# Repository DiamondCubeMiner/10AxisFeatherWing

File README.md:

# 10AxisFeatherWing #
A 10-DOF Featherwing, powered by BNO055 and BME280.

## Description ##
This featherwing uses I2C to connect both the IMU (BNO055) and the altimeter (BME280) to the Feather.
I made this to design projects that require a 10-DOF IMU in a tiny package where breakouts can affect the weight a lot and may not be a good option, such as a quadcopter, a model plane, or a model rocket.

## Drivers ##
This project is designed to use [Adafruit Unified Sensor Drivers](https://github.com/adafruit/Adafruit_Sensor).
  - [Adafruit_BNO055](https://github.com/adafruit/Adafruit_BNO055)
  - [Adafruit_BME280_Library](https://github.com/adafruit/Adafruit_BME280_Library/)

If you are experiencing problems with the Adafruit_BME280_Library, you may use Seeed Studio's [Grove_BME280](https://github.com/Seeed-Studio/Grove_BME280) drivers. It has been tested to work with the 10AxisFeatherWing.

## Thanks ##
This project is derived from the following projects:
  - [Adafruit-ADXL343-ADT7410-Featherwing-PCB](https://github.com/adafruit/Adafruit-ADXL343-ADT7410-Featherwing-PCB)
  - [Adafruit-BNO055-Breakout-PCB](https://github.com/adafruit/Adafruit-BNO055-Breakout-PCB)
  - [Adafruit-BME280-Breakout-PCB](https://github.com/adafruit/Adafruit-BME280-Breakout-PCB)

Thanks to Adafruit for their open-source schematics!

Thanks to ppelleti for the awesome FeatherWing Template!

[FeatherWing-template-KiCad](https://github.com/ppelleti/FeatherWing-template-KiCad)

## License ##
This work is licensed under the Creative Commons Attribution-ShareAlike 3.0 Unported License. To view a copy of this license, visit http://creativecommons.org/licenses/by-sa/3.0/ or by opening license.txt included in this project.

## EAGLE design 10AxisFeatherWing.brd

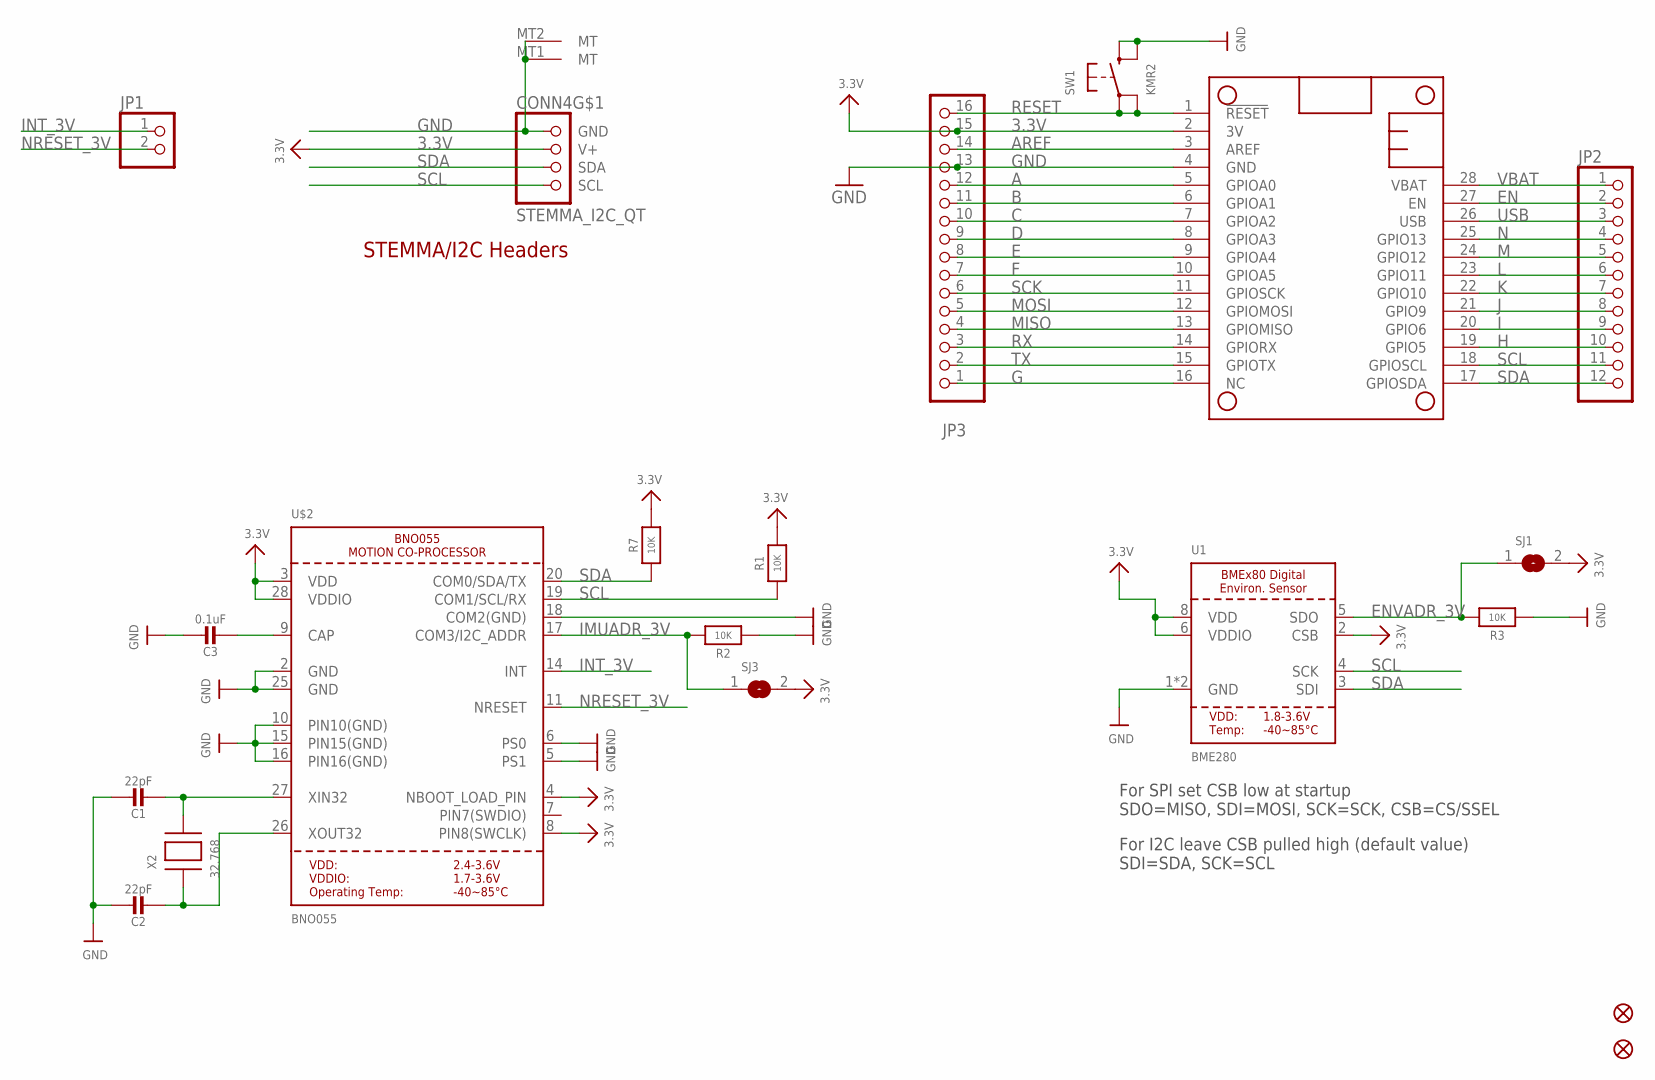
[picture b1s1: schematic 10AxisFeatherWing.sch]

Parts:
C1, C2: 22pF; 0603-NO
C3: 0.1uF; 0603-NO
CONN4: STEMMA_I2C_QT; JST_SH4
FID1, FID2: FIDUCIAL_1MM
JP1: HEADER-1X2ROUND; 1X02_ROUND
JP2: HEADER-1X12; 1X12_ROUND
JP3: HEADER-1X16ROUND; 1X16_ROUND
MS1: FEATHERWING
R1, R2, R3, R7: 10K; 0603-NO
SJ1, SJ3: SOLDERJUMPER; SOLDERJUMPER_ARROW_NOPASTE
SW1: KMR2; BTN_KMR2_4.6X2.8
U1: BME280
U$2: BNO055
X2: 32.768; XTAL3215

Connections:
3.3V: CONN4.2 (V+), JP3.15, MS1.2 (3V), R1.2, R7.2, SJ1.2, SJ3.2, U1.2 (CSB), U1.6 (VDDIO), U1.8 (VDD), U$2.3 (VDD), U$2.4 (NBOOT_LOAD_PIN), U$2.8 (PIN8(SWCLK)), U$2.28 (VDDIO)
A: JP3.12, MS1.5 (GPIOA0)
AREF: JP3.14, MS1.3 (AREF)
B: JP3.11, MS1.6 (GPIOA1)
C: JP3.10, MS1.7 (GPIOA2)
D: JP3.9, MS1.8 (GPIOA3)
E: JP3.8, MS1.9 (GPIOA4)
EN: JP2.2, MS1.27 (EN)
ENVADR_3V: R3.2, SJ1.1, U1.5 (SDO)
F: JP3.7, MS1.10 (GPIOA5)
G: JP3.1, MS1.16 (NC)
GND: C1.1, C2.1, C3.1, CONN4.1 (GND), CONN4.MT1 (MT), CONN4.MT2 (MT), JP3.13, MS1.4 (GND), R2.1, R3.1, SW1.B (S), SW1.B' (S1), U1.1 (GND), U1.7 (GND), U$2.2 (GND), U$2.5 (PS1), U$2.6 (PS0), U$2.10 (PIN10(GND)), U$2.15 (PIN15(GND)), U$2.16 (PIN16(GND)), U$2.18 (COM2(GND)), U$2.25 (GND)
H: JP2.10, MS1.19 (GPIO5)
I: JP2.9, MS1.20 (GPIO6)
IMUADR_3V: R2.2, SJ3.1, U$2.17 (COM3/I2C_ADDR)
INT_3V: JP1.1, U$2.14 (INT)
J: JP2.8, MS1.21 (GPIO9)
K: JP2.7, MS1.22 (GPIO10)
L: JP2.6, MS1.23 (GPIO11)
M: JP2.5, MS1.24 (GPIO12)
MISO: JP3.4, MS1.13 (GPIOMISO)
MOSI: JP3.5, MS1.12 (GPIOMOSI)
N: JP2.4, MS1.25 (GPIO13)
unnamed: C1.2, U$2.27 (XIN32), X2.P$2
unnamed: C2.2, U$2.26 (XOUT32), X2.P$1
unnamed: C3.2, U$2.9 (CAP)
NRESET_3V: JP1.2, U$2.11 (NRESET)
RESET: JP3.16, MS1.1 (!RESET), SW1.A, SW1.A' (P1)
RX: JP3.3, MS1.14 (GPIORX)
SCK: JP3.6, MS1.11 (GPIOSCK)
SCL: CONN4.4 (SCL), JP2.11, MS1.18 (GPIOSCL), R1.1, U1.4 (SCK), U$2.19 (COM1/SCL/RX)
SDA: CONN4.3 (SDA), JP2.12, MS1.17 (GPIOSDA), R7.1, U1.3 (SDI), U$2.20 (COM0/SDA/TX)
TX: JP3.2, MS1.15 (GPIOTX)
USB: JP2.3, MS1.26 (USB)
VBAT: JP2.1, MS1.28 (VBAT)

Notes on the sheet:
STEMMA/I2C Headers
For SPI set CSB low at startup SDO=MISO, SDI=MOSI, SCK=SCK, CSB=CS/SSEL
For I2C leave CSB pulled high (default value) SDI=SDA, SCK=SCL

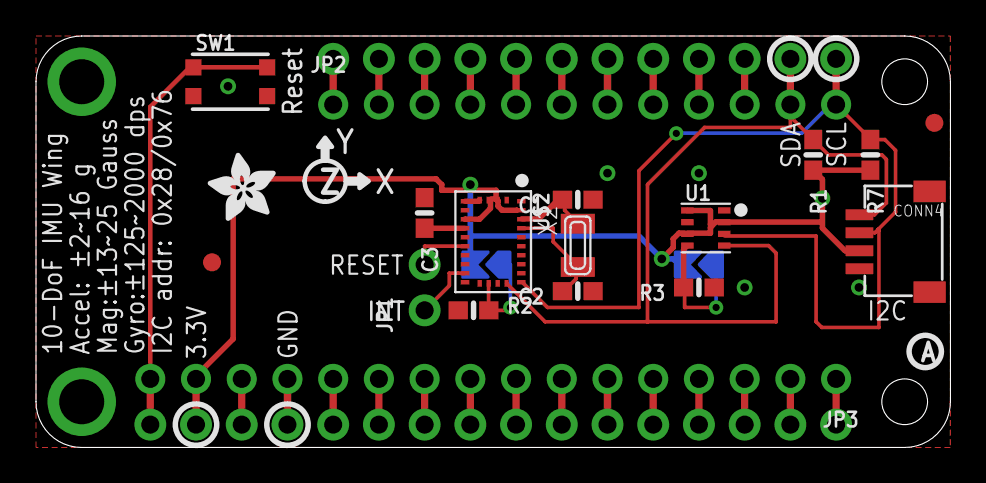
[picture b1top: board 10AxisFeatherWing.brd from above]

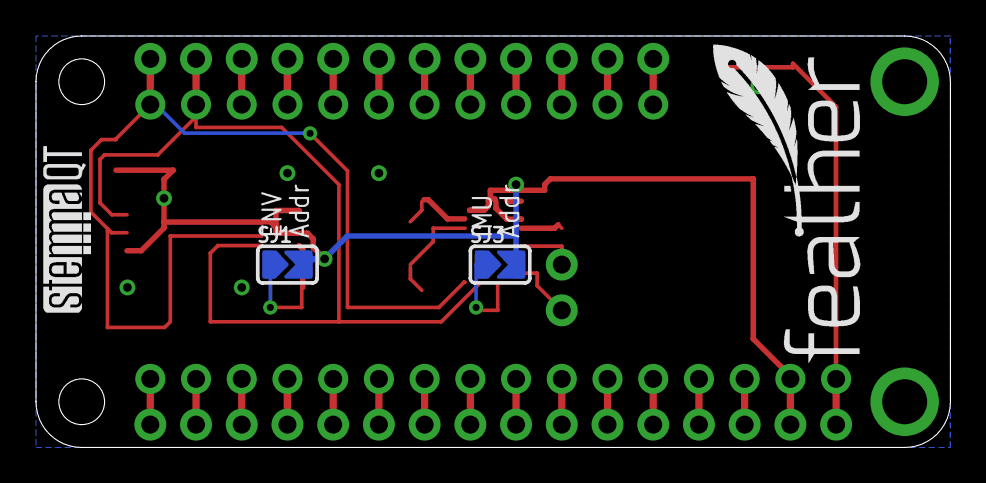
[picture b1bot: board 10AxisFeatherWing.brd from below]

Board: 2 copper layers, 50.8 x 22.9 mm, 24 parts (4 on the bottom side), 35 nets.

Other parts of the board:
U$13: FEATHERLOGO_MED
U$31: STEMMAQT
U$50: ADAFRUIT_3.5MM
U$51: PCBFEAT-REV-040

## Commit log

2019-12-20 Initial upload
2019-12-20 Update README.md
    Added a line break fix on the Thanks section.
2019-12-22 Fixed IMU VDDIO not connected
2019-12-24 Added new features
    Added RESET button, INT breakout, and silk text.
2019-12-26 Corrected crystal capacitor values
2019-12-31 Migration to KiCad
2020-01-05 Updated features
    Replaced NRESET with pin instead of a button, Added silk text
2020-01-07 Minor format fix
2020-01-12 Increased trace width
2020-01-13 Updated PCB
2020-02-06 Fixed electrical connections
    Fixed the following electrical connection errors:
    > Pin 6 on BNO055 not connected to GND
    > SDA and SCL vias too close
    > Pin 18 on BNO055 GND relocated
2020-02-06 Removed STEMMA connector
    STEMMA connectors should have 3.3V to 5V level shifting and power regulation.
    This board does not have those features, so they were removed.
2020-02-06 Revert "Removed STEMMA connector"
    This reverts commit 5727fb72f54931faedf32c304c5adffcc3f247c0.
2020-02-07 Fixed C7 not connected to BME280 pin 6
    C7 is a decoupling capacitor, and should be connected to both VDD.
2020-04-09 Update README.md
    Added troubleshooting for BME280 library.
2020-09-23 EagleCAD Refactor
    - Switched to EagleCAD. Now uses microbuilder.lbr used by Adafruit Industries
    - Removed filter caps
    - Added STEMMA connector
    - Adafruit Logo! Heavily based on their latest 9-DoF Combo featherwings (Should I remove it?)
2020-11-12 Revert "EagleCAD Refactor"
    This reverts commit e0a2de9822f84c03f4477eba47b3f3700a9858d7.
2020-11-16 I2C pull-up resistor fix
    Changed I2C pull-up resistor values from 10K to 4.7K

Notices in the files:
parts and their libraries:
microbuilder: This work is placed in the public domain, and may be freely used for commercial and non-commercial work with the following conditions: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
